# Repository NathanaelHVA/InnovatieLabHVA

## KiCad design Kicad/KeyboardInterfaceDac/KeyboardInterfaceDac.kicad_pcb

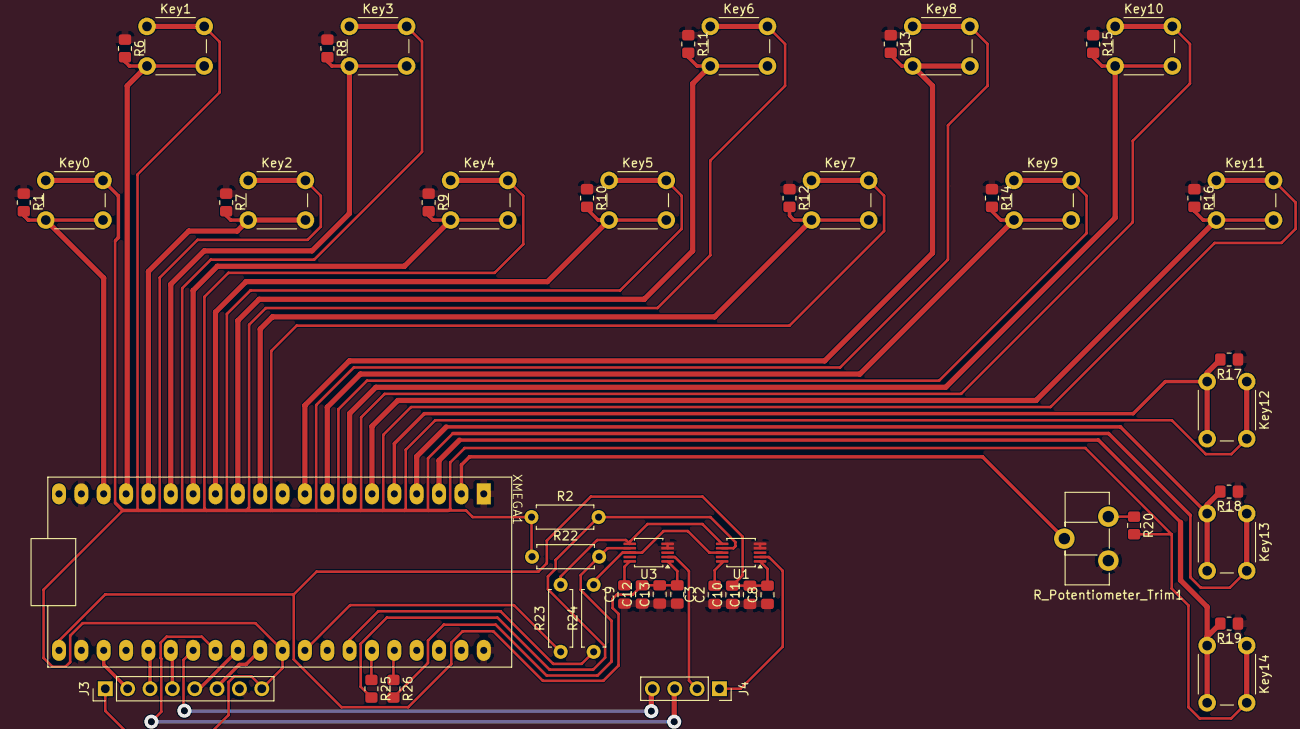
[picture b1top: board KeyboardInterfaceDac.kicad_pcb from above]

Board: 2 copper layers, 51 parts (0 on the bottom side), 38 nets.

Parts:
C2, C9: 220nF; C_0805_2012Metric_Pad1.18x1.45mm_HandSolder
C3, C8: 100nF; C_0805_2012Metric_Pad1.18x1.45mm_HandSolder
C10, C12: 0,22uF; C_0805_2012Metric_Pad1.18x1.45mm_HandSolder
C11, C13: 4,7uF; C_0805_2012Metric_Pad1.18x1.45mm_HandSolder
J3: Interface tft; PinHeader_1x08_P2.54mm_Vertical
J4: Output; PinSocket_1x04_P2.54mm_Vertical
Key0, Key1, Key2, Key3, Key4, Key5, Key6, Key7, Key8, Key9, Key10, Key11: Keyboard; SW_PUSH_6mm_H7.3mm
Key12: OctaafSelector; SW_PUSH_6mm_H7.3mm
Key13: SignaalSelector1; SW_PUSH_6mm_H7.3mm
Key14: SignaalSelector2; SW_PUSH_6mm_H7.3mm
R1, R6, R7, R8, R9, R10, R11, R12, R13, R14, R15, R16, R17, R18, R19: 10K; R_0805_2012Metric_Pad1.20x1.40mm_HandSolder
R2, R22: 10k; R_Axial_DIN0207_L6.3mm_D2.5mm_P7.62mm_Horizontal
R20: 900; R_0805_2012Metric_Pad1.20x1.40mm_HandSolder
R23, R24: 100; R_Axial_DIN0207_L6.3mm_D2.5mm_P7.62mm_Horizontal
R25, R26: 100; R_0805_2012Metric_Pad1.20x1.40mm_HandSolder
R_Potentiometer_Trim1: Potmeter/Spanningsdeler; Potentiometer_Piher_PT-10-H05_Horizontal
U1, U3: DAC80502; TSSOP-10_3x3mm_P0.5mm
XMEGA1: XMEGABoard-Rev1.11; HvA_XMEGABoard-rev1.00-S

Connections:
+5V: C3.2, C8.2, C10.2, C11.2, C12.2, C13.2, U1.1 (VDD), U3.1 (VDD), XMEGA1.21 (5V_IN)
/CS: R2.2, R22.2, R25.2, R26.2, U1.7 (~SYNC/A0), U3.7 (~SYNC/A0)
/Mosi: R24.2, U1.8 (SDIN/SDA), U3.8 (SDIN/SDA)
/SCK: R23.2, U1.6 (SCLK/SCL), U3.6 (SCLK/SCL)
GND: C2.1, C3.1, C8.1, C9.1, C10.1, C11.1, C12.1, C13.1, J3.7, R1.1, R6.1, R7.1, R8.1, R9.1, R10.1, R11.1, R12.1, R13.1, R14.1, R15.1, R16.1, R17.1, R18.1, R19.1, R_Potentiometer_Trim1.1, U1.4 (AGND), U1.5 (SPI2C), U3.4 (AGND), U3.5 (SPI2C), XMEGA1.01 (GND), XMEGA1.10 (GND), XMEGA1.19 (GND), XMEGA1.22 (GND), XMEGA1.40 (GND)
unnamed: J3.1, J3.8, Key0.1 (A), Key1.1 (A), Key2.1 (A), Key3.1 (A), Key4.1 (A), Key5.1 (A), Key6.1 (A), Key7.1 (A), Key8.1 (A), Key9.1 (A), Key10.1 (A), Key11.1 (A), Key12.1 (A), Key13.1 (A), Key14.1 (A), R2.1, R20.2, R22.1, XMEGA1.31 (3V3)
unnamed: J3.2, XMEGA1.23 (PE7)
unnamed: J3.3, XMEGA1.25 (PE5)
unnamed: J3.4, XMEGA1.26 (PE4)
unnamed: J3.5, XMEGA1.29 (PE1)
unnamed: J3.6, XMEGA1.30 (PE0)
unnamed: J4.3, XMEGA1.28 (PE2)
unnamed: J4.4, XMEGA1.27 (PE3)
unnamed: Key0.2 (B), R1.2, XMEGA1.18 (PA0)
unnamed: Key1.2 (B), R6.2, XMEGA1.17 (PA1)
unnamed: Key2.2 (B), R7.2, XMEGA1.16 (PA2)
unnamed: Key3.2 (B), R8.2, XMEGA1.15 (PA3)
unnamed: Key4.2 (B), R9.2, XMEGA1.14 (PA4)
unnamed: Key5.2 (B), R10.2, XMEGA1.13 (PA5)
unnamed: Key6.2 (B), R11.2, XMEGA1.12 (PA6)
unnamed: Key7.2 (B), R12.2, XMEGA1.11 (PA7)
unnamed: Key8.2 (B), R13.2, XMEGA1.09 (PB0)
unnamed: Key9.2 (B), R14.2, XMEGA1.08 (PB1)
unnamed: Key10.2 (B), R15.2, XMEGA1.07 (PB2)
unnamed: Key11.2 (B), R16.2, XMEGA1.06 (PB3)
unnamed: Key12.2 (B), R17.2, XMEGA1.05 (PB4)
unnamed: Key13.2 (B), R18.2, XMEGA1.04 (PB5)
unnamed: Key14.2 (B), R19.2, XMEGA1.03 (PB6)
unnamed: R20.1, R_Potentiometer_Trim1.3
unnamed: C2.2, U1.10 (VREFIO)
unnamed: C9.2, U3.10 (VREFIO)
unnamed: R_Potentiometer_Trim1.2, XMEGA1.02 (PB7)
unnamed: R26.1, XMEGA1.36 (PD3)
unnamed: R25.1, XMEGA1.35 (PD4)
unnamed: R24.1, XMEGA1.34 (PD5)
unnamed: R23.1, XMEGA1.32 (PD7)
Vout1: J4.1, U1.2 (VOUTA)
Vout2: J4.2, U3.2 (VOUTA)

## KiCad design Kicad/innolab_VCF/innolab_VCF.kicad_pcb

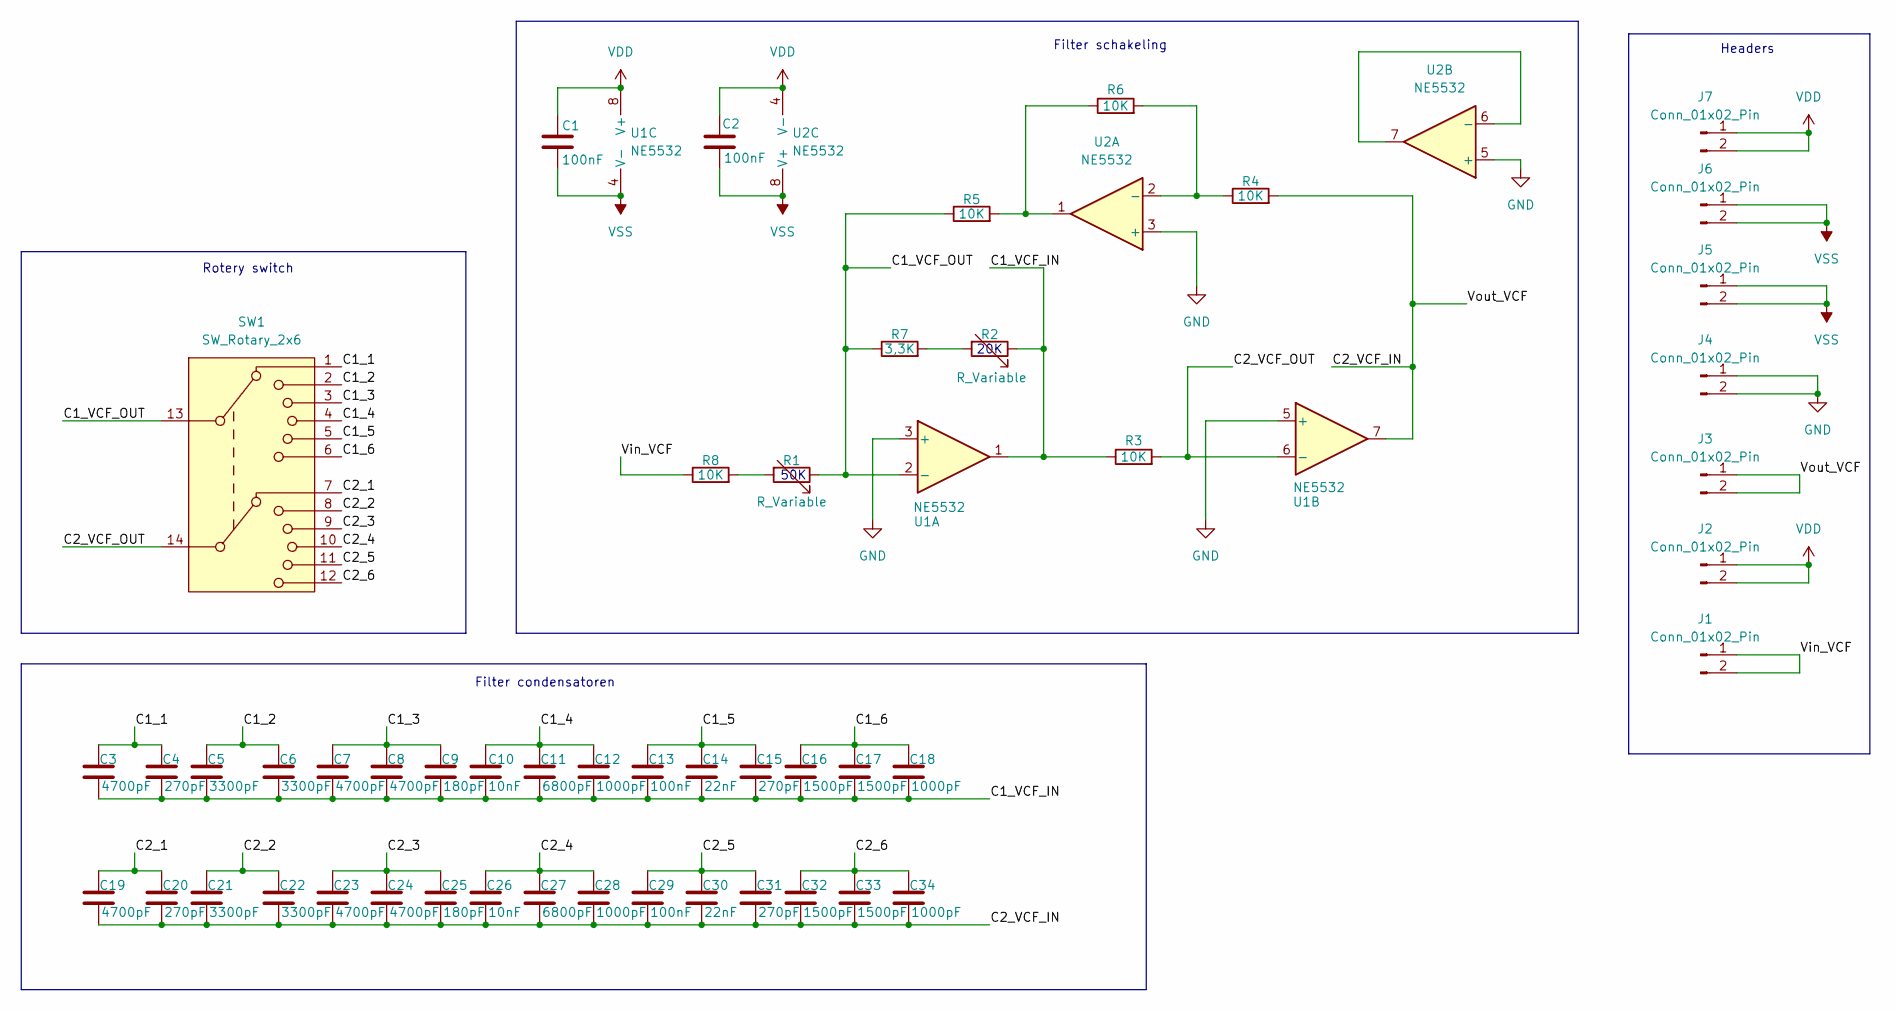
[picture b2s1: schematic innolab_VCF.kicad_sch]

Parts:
C1, C2: 100nF; C_0805_2012Metric_Pad1.18x1.45mm_HandSolder
C3, C7, C8, C19, C23, C24: 4700pF; C_Rect_L7.0mm_W2.0mm_P5.00mm
C4, C15, C20, C31: 270pF; C_0805_2012Metric
C5, C6, C21, C22: 3300pF; C_Rect_L7.0mm_W2.0mm_P5.00mm
C9, C25: 180pF; C_0805_2012Metric
C10, C26: 10nF; C_Rect_L7.0mm_W2.0mm_P5.00mm
C11, C27: 6800pF; C_Rect_L7.0mm_W2.0mm_P5.00mm
C12, C18, C28, C34: 1000pF; C_Rect_L7.0mm_W2.0mm_P5.00mm
C13, C29: 100nF; C_Rect_L7.0mm_W2.0mm_P5.00mm
C14, C30: 22nF; C_Rect_L7.0mm_W2.0mm_P5.00mm
C16, C17, C32, C33: 1500pF; C_Rect_L7.0mm_W2.0mm_P5.00mm
J1, J2, J3, J4, J5, J6, J7: Conn_01x02_Pin; PinHeader_1x02_P2.54mm_Vertical
R1, R2: R_Variable; Potentiometer_Piher_PT-10-H05_Horizontal
R3, R4, R5, R6, R8: 10K; R_0805_2012Metric_Pad1.20x1.40mm_HandSolder
R7: 3,3K; R_0805_2012Metric_Pad1.20x1.40mm_HandSolder
SW1: SW_Rotary_2x6; CK1035
U1, U2: NE5532; SOIC-8_3.9x4.9mm_P1.27mm

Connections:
/C1_1: C3.1, C4.1, SW1.1
/C1_2: C5.1, C6.1, SW1.2
/C1_3: C7.1, C8.1, C9.1, SW1.3
/C1_4: C10.1, C11.1, C12.1, SW1.4
/C1_5: C13.1, C14.1, C15.1, SW1.5
/C1_6: C16.1, C17.1, C18.1, SW1.6
/C1_VCF_IN: C3.2, C4.2, C5.2, C6.2, C7.2, C8.2, C9.2, C10.2, C11.2, C12.2, C13.2, C14.2, C15.2, C16.2, C17.2, C18.2, R2.1, R3.1, U1.1
/C1_VCF_OUT: R1.1, R5.1, R7.1, SW1.13, U1.2 (-)
/C2_1: C19.1, C20.1, SW1.7
/C2_2: C21.1, C22.1, SW1.8
/C2_3: C23.1, C24.1, C25.1, SW1.9
/C2_4: C26.1, C27.1, C28.1, SW1.10
/C2_5: C29.1, C30.1, C31.1, SW1.11
/C2_6: C32.1, C33.1, C34.1, SW1.12
/C2_VCF_IN: C19.2, C20.2, C21.2, C22.2, C23.2, C24.2, C25.2, C26.2, C27.2, C28.2, C29.2, C30.2, C31.2, C32.2, C33.2, C34.2, J3.1, J3.2, R4.2, U1.7
/C2_VCF_OUT: R3.2, SW1.14, U1.6 (-)
/Vin_VCF: J1.1, J1.2, R8.1
GND: J4.1, J4.2, U1.3 (+), U1.5 (+), U2.3 (+), U2.5 (+)
unnamed: R1.2, R8.2
unnamed: R2.2, R7.2
unnamed: R5.2, R6.1, U2.1
unnamed: R4.1, R6.2, U2.2 (-)
unnamed: U2.6 (-), U2.7
VDD: C1.1, C2.1, J2.1, J2.2, J7.1, J7.2, U1.8 (V+), U2.4 (V-)
VSS: C1.2, C2.2, J5.1, J5.2, J6.1, J6.2, U1.4 (V-), U2.8 (V+)

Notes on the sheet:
Filter schakeling
Rotery switch
50K
Filter condensatoren
20K
Headers

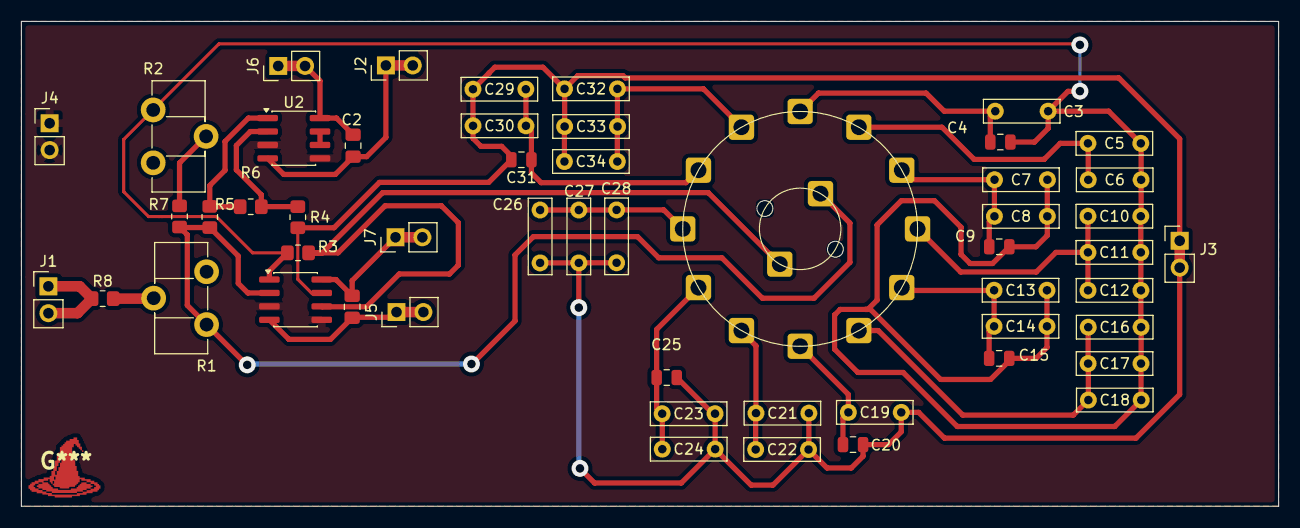
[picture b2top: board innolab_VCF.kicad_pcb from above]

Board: 2 copper layers, 118.9 x 45.8 mm, 52 parts (0 on the bottom side), 25 nets.

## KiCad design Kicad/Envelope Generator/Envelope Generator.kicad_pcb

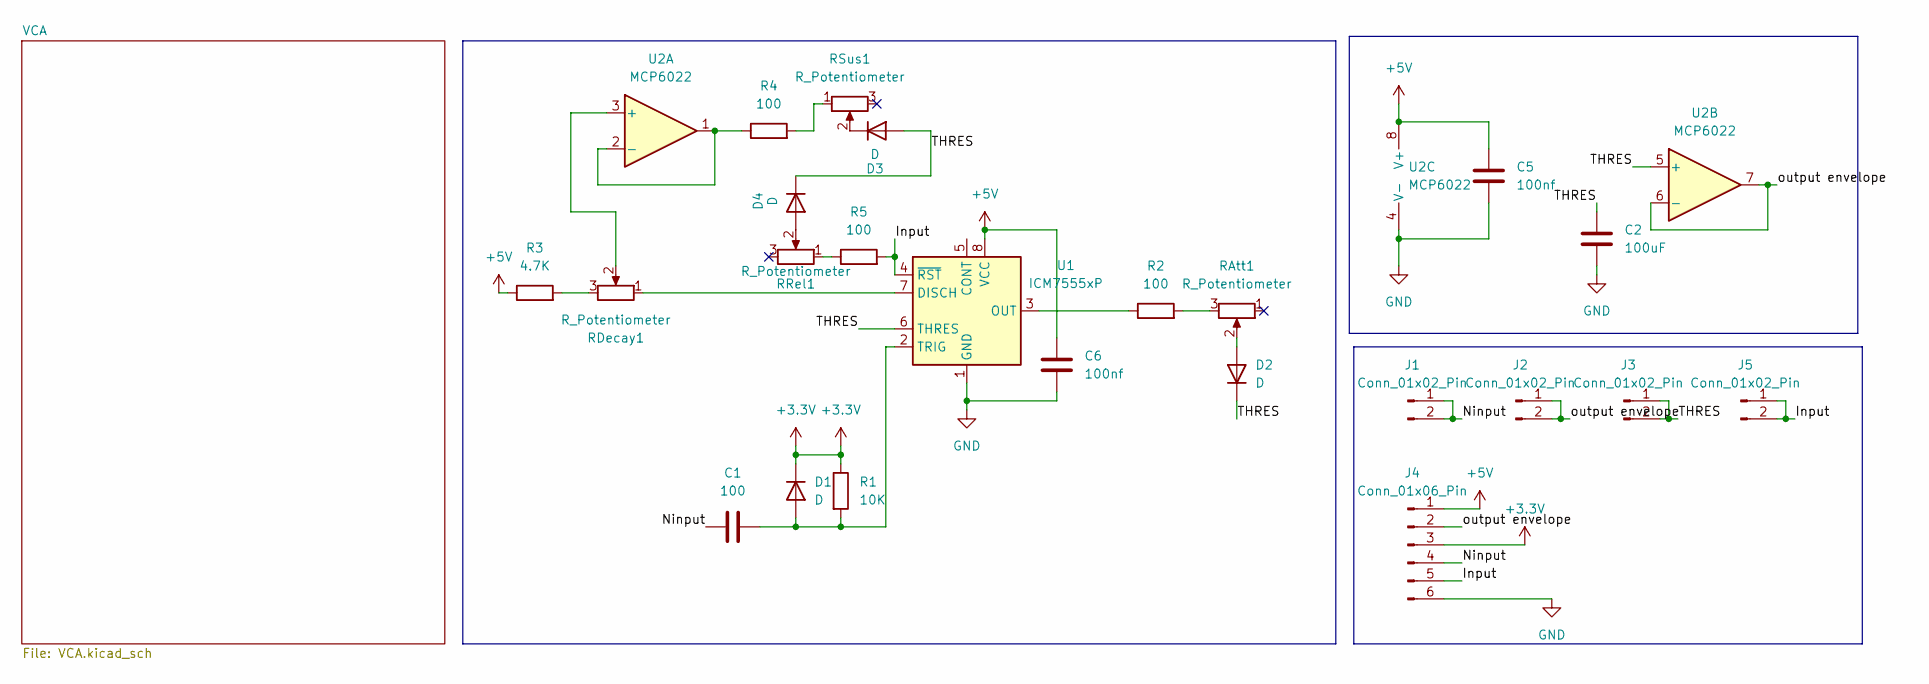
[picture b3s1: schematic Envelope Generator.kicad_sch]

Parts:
C1: 100; C_0805_2012Metric_Pad1.18x1.45mm_HandSolder
C2: 100uF; C_0805_2012Metric_Pad1.18x1.45mm_HandSolder
C5, C6: 100nf; C_0805_2012Metric_Pad1.18x1.45mm_HandSolder
D1, D2, D3, D4: D; D_0805_2012Metric_Pad1.15x1.40mm_HandSolder
J1, J2, J3, J5: Conn_01x02_Pin; PinHeader_1x02_P2.54mm_Vertical
J4: Conn_01x06_Pin; PinHeader_1x06_P2.54mm_Vertical
R1: 10K; R_0805_2012Metric_Pad1.20x1.40mm_HandSolder
R2, R4, R5: 100; R_0805_2012Metric_Pad1.20x1.40mm_HandSolder
R3: 4.7K; R_0805_2012Metric_Pad1.20x1.40mm_HandSolder
RAtt1: R_Potentiometer; Potentiometer_Piher_PT-10-H05_Horizontal
RDecay1: R_Potentiometer; Potentiometer_Piher_PT-10-H05_Horizontal
RRel1: R_Potentiometer; Potentiometer_Piher_PT-10-H05_Horizontal
RSus1: R_Potentiometer; Potentiometer_Piher_PT-10-H05_Horizontal
U1: ICM7555xP; DIP-8_W7.62mm
U2: MCP6022; SOIC-8_3.9x4.9mm_P1.27mm

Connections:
+3.3V: D1.1 (K), J4.3, R1.1
+5V: C5.2, C6.2, J4.1, R3.1, U1.8 (VCC), U2.8 (V+); also elsewhere on the board
/Input: J4.5, J5.1, J5.2, R5.2, U1.4 (~RST)
/Ninput: C1.1, J1.1, J1.2, J4.4
/THRES: C2.2, D2.1 (K), D3.2 (A), D4.1 (K), J3.1, J3.2, U1.6 (THRES), U2.5 (+)
/output envelope: J2.1, J2.2, J4.2, U2.6 (-), U2.7
GND: C2.1, C5.1, C6.1, J4.6, U1.1 (GND), U2.4 (V-); also elsewhere on the board
unnamed: C1.2, D1.2 (A), R1.2, U1.2 (TRIG)
unnamed: D2.2 (A), RAtt1.2
unnamed: D3.1 (K), RSus1.2
unnamed: D4.2 (A), RRel1.2
unnamed: R2.2, RAtt1.3
unnamed: R3.2, RDecay1.3
unnamed: R4.2, RSus1.1
unnamed: R5.1, RRel1.1
unnamed: RDecay1.1, U1.7 (DISCH)
unnamed: R2.1, U1.3 (OUT)
unnamed: RDecay1.2, U2.3 (+)
unnamed: R4.1, U2.1, U2.2 (-)

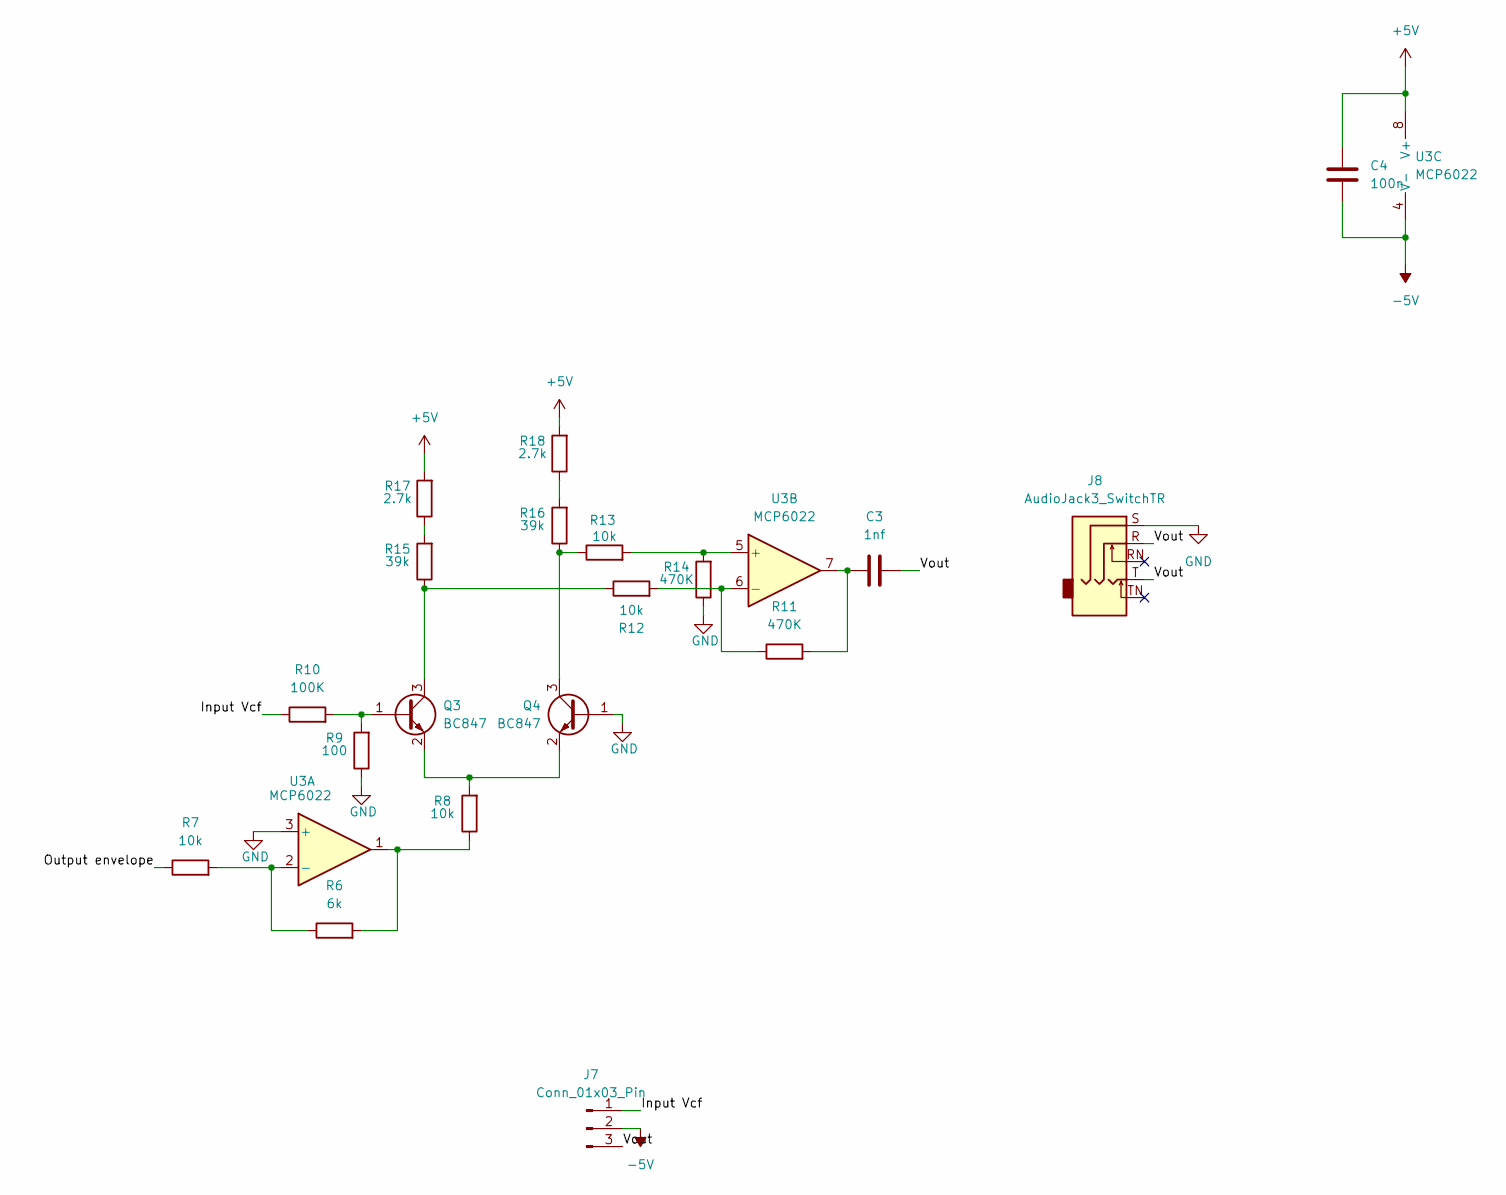
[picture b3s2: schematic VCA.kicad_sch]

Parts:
C3: 1nf; C_0805_2012Metric_Pad1.18x1.45mm_HandSolder
C4: 100n; C_0805_2012Metric_Pad1.18x1.45mm_HandSolder
J7: Conn_01x03_Pin; PinHeader_1x03_P2.54mm_Vertical
J8: AudioJack3_SwitchTR; Jack_3.5mm_CUI_SJ1-3525N_Horizontal
Q3, Q4: BC847; SOT-23
R6: 6k; C_0805_2012Metric_Pad1.18x1.45mm_HandSolder
R7, R8, R12, R13: 10k; C_0805_2012Metric_Pad1.18x1.45mm_HandSolder
R9: 100; C_0805_2012Metric_Pad1.18x1.45mm_HandSolder
R10: 100K; C_0805_2012Metric_Pad1.18x1.45mm_HandSolder
R11, R14: 470K; C_0805_2012Metric_Pad1.18x1.45mm_HandSolder
R15, R16: 39k; C_0805_2012Metric_Pad1.18x1.45mm_HandSolder
R17, R18: 2.7k; C_0805_2012Metric_Pad1.18x1.45mm_HandSolder
U3: MCP6022; SOIC-8_3.9x4.9mm_P1.27mm

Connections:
+5V: C4.2, R17.2, R18.2, U3.8 (V+); also elsewhere on the board
-5V: C4.1, J7.2, U3.4 (V-)
/VCA/Input Vcf: J7.1, R10.1
/VCA/Output envelope: R7.1
/VCA/Vout: C3.2, J7.3, J8.R, J8.T
GND: J8.S, Q4.1 (B), R9.1, R14.1, U3.3 (+); also elsewhere on the board
unnamed: C3.1, R11.2, U3.7
unnamed: Q3.1 (B), R9.2, R10.2
unnamed: Q3.3 (C), R12.1, R15.1
unnamed: Q3.2 (E), Q4.2 (E), R8.2
unnamed: Q4.3 (C), R13.1, R16.1
unnamed: R6.2, R8.1, U3.1
unnamed: R15.2, R17.1
unnamed: R16.2, R18.1
unnamed: R6.1, R7.2, U3.2 (-)
unnamed: R13.2, R14.2, U3.5 (+)
unnamed: R11.1, R12.2, U3.6 (-)

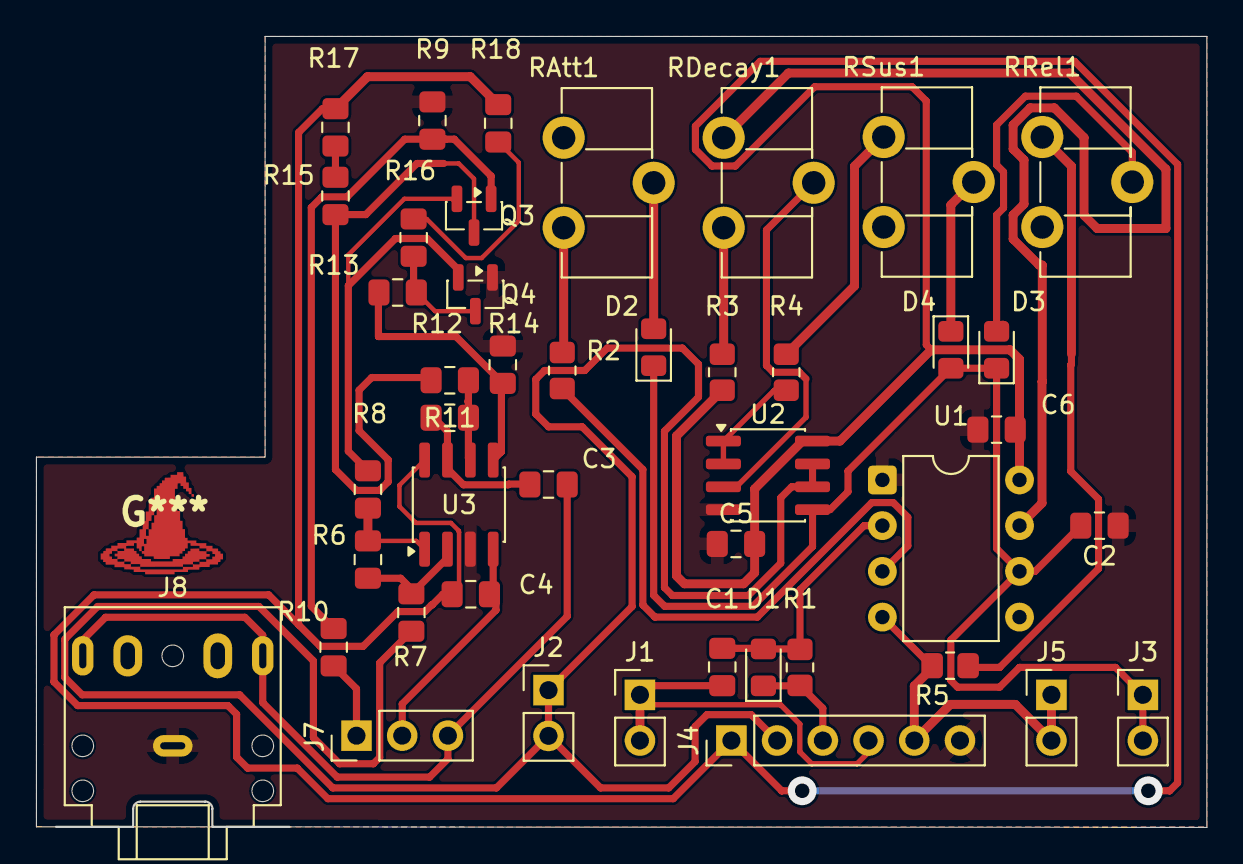
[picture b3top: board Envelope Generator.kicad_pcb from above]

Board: 2 copper layers, 65.0 x 43.9 mm, 44 parts (0 on the bottom side), 33 nets.

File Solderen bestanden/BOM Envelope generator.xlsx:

Stuklijst (BOM)
Geëxporteerd uit KiCad · 10-11-2026 · gegroepeerd per componenttype
Referentie | Aantal | Waarde | Type | Montage | Footprint | Datasheet | KiCad-footprint (volledig)
U1 | 1 | ICM7555xP | IC | THT | DIP-8 | ICM7555 datasheet (Intersil) | Package_DIP:DIP-8_W7.62mm
U2, U3 | 2 | MCP6022 | IC | SMD | SOIC-8 | MCP6022 datasheet (Microchip) | Package_SO:SOIC-8_3.9x4.9mm_P1.27mm
Q3, Q4 | 2 | BC847 | Transistor | SMD | SOT-23 | BC847 datasheet (Infineon) | Package_TO_SOT_SMD:SOT-23
D1, D2, D3, D4 | 4 | Diode (type ontbreekt) | Diode | SMD | 0805 |  | Diode_SMD:D_0805_2012Metric_Pad1.15x1.40mm_HandSolder
C1 | 1 | 100 | Condensator | SMD | 0805 |  | Capacitor_SMD:C_0805_2012Metric_Pad1.18x1.45mm_HandSolder
C2 | 1 | 100 µF | Condensator | SMD | 0805 |  | Capacitor_SMD:C_0805_2012Metric_Pad1.18x1.45mm_HandSolder
C3 | 1 | 1 nF | Condensator | SMD | 0805 |  | Capacitor_SMD:C_0805_2012Metric_Pad1.18x1.45mm_HandSolder
C4 | 1 | 100 nF | Condensator | SMD | 0805 |  | Capacitor_SMD:C_0805_2012Metric_Pad1.18x1.45mm_HandSolder
C5, C6 | 2 | 100 nF | Condensator | SMD | 0805 |  | Capacitor_SMD:C_0805_2012Metric_Pad1.18x1.45mm_HandSolder
R1 | 1 | 10 kΩ | Weerstand | SMD | 0805 |  | Resistor_SMD:R_0805_2012Metric_Pad1.20x1.40mm_HandSolder
R2, R4, R5 | 3 | 100 Ω | Weerstand | SMD | 0805 |  | Resistor_SMD:R_0805_2012Metric_Pad1.20x1.40mm_HandSolder
R3 | 1 | 4,7 kΩ | Weerstand | SMD | 0805 |  | Resistor_SMD:R_0805_2012Metric_Pad1.20x1.40mm_HandSolder
R6 | 1 | 6 kΩ | Weerstand | SMD | 0805 |  | Capacitor_SMD:C_0805_2012Metric_Pad1.18x1.45mm_HandSolder
R7, R8, R12, R13 | 4 | 10 kΩ | Weerstand | SMD | 0805 |  | Capacitor_SMD:C_0805_2012Metric_Pad1.18x1.45mm_HandSolder
R9 | 1 | 100 Ω | Weerstand | SMD | 0805 |  | Capacitor_SMD:C_0805_2012Metric_Pad1.18x1.45mm_HandSolder
R10 | 1 | 100 kΩ | Weerstand | SMD | 0805 |  | Capacitor_SMD:C_0805_2012Metric_Pad1.18x1.45mm_HandSolder
R11, R14 | 2 | 470 kΩ | Weerstand | SMD | 0805 |  | Capacitor_SMD:C_0805_2012Metric_Pad1.18x1.45mm_HandSolder
R15, R16 | 2 | 39 kΩ | Weerstand | SMD | 0805 |  | Capacitor_SMD:C_0805_2012Metric_Pad1.18x1.45mm_HandSolder
R17, R18 | 2 | 2,7 kΩ | Weerstand | SMD | 0805 |  | Capacitor_SMD:C_0805_2012Metric_Pad1.18x1.45mm_HandSolder
RAtt1, RDecay1, RRel1, RSus1 | 4 | Potmeter (waarde ontbreekt) | Potmeter | THT | Piher PT-10-H05, horizontaal |  | Potentiometer_THT:Potentiometer_Piher_PT-10-H05_Horizontal
J1, J2, J3, J5 | 4 | Pinheader 1x02 | Connector | THT | Pinheader 1x02, 2,54 mm |  | Connector_PinHeader_2.54mm:PinHeader_1x02_P2.54mm_Vertical
J4 | 1 | Pinheader 1x06 | Connector | THT | Pinheader 1x06, 2,54 mm |  | Connector_PinHeader_2.54mm:PinHeader_1x06_P2.54mm_Vertical
J7 | 1 | Pinheader 1x03 | Connector | THT | Pinheader 1x03, 2,54 mm |  | Connector_PinHeader_2.54mm:PinHeader_1x03_P2.54mm_Vertical
J8 | 1 | Audiojack 3,5 mm (TR, schakelend) | Connector | THT | Jack 3,5 mm CUI SJ1-3525N, horizontaal |  | Connector_Audio:Jack_3.5mm_CUI_SJ1-3525N_Horizontal
Totaal | 44
Het totaal past zich aan als je de filter gebruikt (SUBTOTAL). Gele cellen in '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

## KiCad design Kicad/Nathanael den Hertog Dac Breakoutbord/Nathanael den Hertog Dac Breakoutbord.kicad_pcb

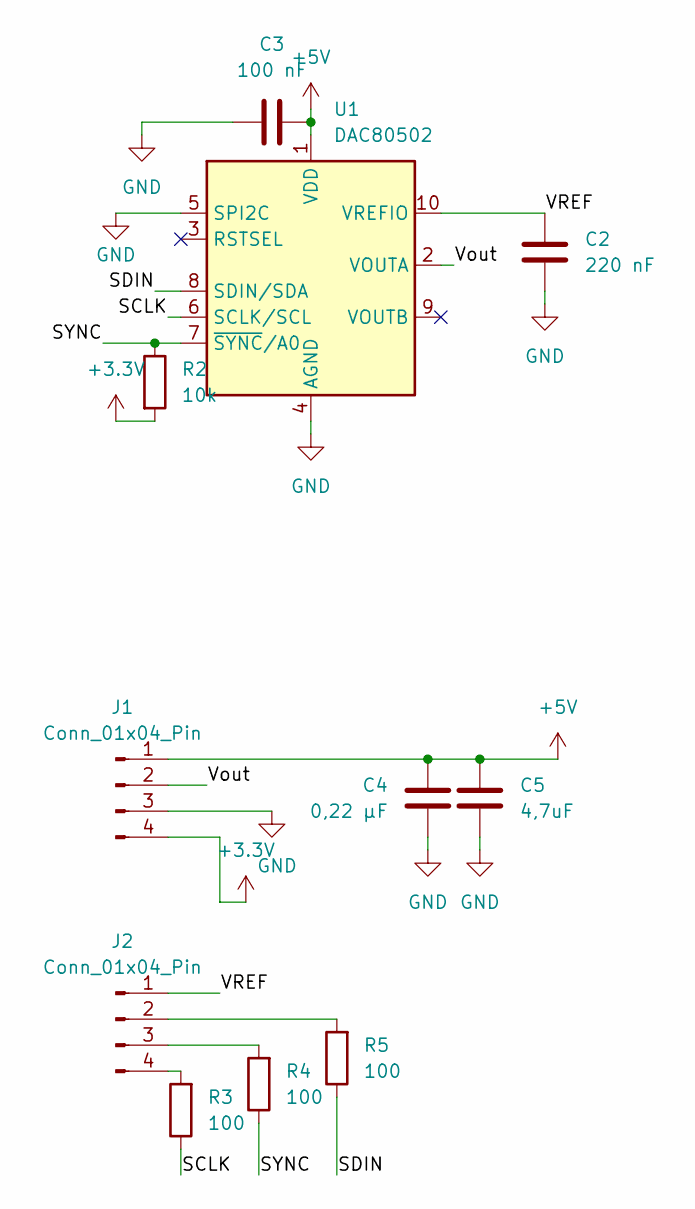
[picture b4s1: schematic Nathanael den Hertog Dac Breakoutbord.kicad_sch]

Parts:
C2: 220 nF; C_0805_2012Metric_Pad1.18x1.45mm_HandSolder
C3: 100 nF; C_0805_2012Metric_Pad1.18x1.45mm_HandSolder
C4: 0,22 µF; C_0805_2012Metric_Pad1.18x1.45mm_HandSolder
C5: 4,7uF; C_0805_2012Metric_Pad1.18x1.45mm_HandSolder
J1, J2: Conn_01x04_Pin; PinHeader_1x04_P2.54mm_Vertical
R2: 10k; R_0805_2012Metric_Pad1.20x1.40mm_HandSolder
R3, R4, R5: 100; R_0805_2012Metric_Pad1.20x1.40mm_HandSolder
U1: DAC80502; TSSOP-10_3x3mm_P0.5mm

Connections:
+3.3V: J1.4, R2.2
+5V: C3.2, C4.2, C5.2, J1.1, U1.1 (VDD)
/SCLK: R3.1, U1.6 (SCLK/SCL)
/SDIN: R5.1, U1.8 (SDIN/SDA)
/SYNC: R2.1, R4.1, U1.7 (~SYNC/A0)
/VREF: C2.1, J2.1, U1.10 (VREFIO)
/Vout: J1.2, U1.2 (VOUTA)
GND: C2.2, C3.1, C4.1, C5.1, J1.3, U1.4 (AGND), U1.5 (SPI2C)
unnamed: J2.2, R5.2
unnamed: J2.3, R4.2
unnamed: J2.4, R3.2

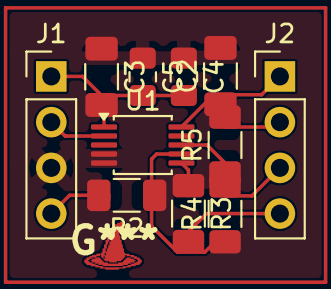
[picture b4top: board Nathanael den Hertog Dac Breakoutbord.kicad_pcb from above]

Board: 2 copper layers, 11 parts (0 on the bottom side), 11 nets.

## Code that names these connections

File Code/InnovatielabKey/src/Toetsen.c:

#include <avr/io.h>
#include "toetsen.h"

// Octaafknop op PB4
#define OCTAAF_PORT     PORTB
#define OCTAAF_PIN_bm   PIN4_bm
#define OCTAAF_PINCTRL  PIN4CTRL
#define OCTAAF_BIT      12     

#define TOETS10_BIT     10
#define TOETS10_PORT    PORTC
#define TOETS10_PIN_bm  PIN0_bm
#define TOETS10_PINCTRL PIN0CTRL

static uint8_t  octaaf         = 0;
static uint16_t vorige_sample  = 0; 
static uint16_t vorige_stabiel = 0;   

void toetsen_init(void)
{
    PORTA.DIRCLR = 0xFF;                 // PA0..PA7 als ingang
    PORTB.DIRCLR = 0x0B;                 // PB0, PB1, PB3 als ingang (PB2 = DAC)
    TOETS10_PORT.DIRCLR = TOETS10_PIN_bm;// PC0 als ingang
    OCTAAF_PORT.DIRCLR = OCTAAF_PIN_bm;  // PB4 als ingang

    // Interne pull-downs
    for (uint8_t i = 0; i < 8; i++)
        (&PORTA.PIN0CTRL)[i] = PORT_OPC_PULLDOWN_gc;
    for (uint8_t i = 0; i < 4; i++)
        if (i != 2)                      // PB2 overslaan, die is de DAC-uitgang
            (&PORTB.PIN0CTRL)[i] = PORT_OPC_PULLDOWN_gc;
    TOETS10_PORT.TOETS10_PINCTRL = PORT_OPC_PULLDOWN_gc;
    OCTAAF_PORT.OCTAAF_PINCTRL = PORT_OPC_PULLDOWN_gc;
}

// Alle knoppen in één 16-bit waarde:
// bit 0..7 = PA0..PA7, bit 8, 9, 11 = PB0, PB1, PB3,
// bit 10 = PC0 (toets 10), bit 12 = octaafknop
static uint16_t lees_knoppen(void)
{
    uint16_t a   = PORTA.IN;
    uint16_t b   = PORTB.IN & 0x0B;      // PB0, PB1, PB3 -> bit 8, 9, 11
    uint16_t t10 = (TOETS10_PORT.IN & TOETS10_PIN_bm) ? 1U : 0U;
    uint16_t o   = (OCTAAF_PORT.IN & OCTAAF_PIN_bm) ? 1U : 0U;

    return a | (b << 8) | (t10 << TOETS10_BIT) | (o << OCTAAF_BIT);
}

toetsen_event_t toetsen_poll(void)
{
    toetsen_event_t ev = {0, 0};
    uint16_t nu = lees_knoppen();

    // Debounce: alleen accepteren als twee polls na elkaar gelijk zijn
    if (nu == vorige_sample) {
        uint16_t nieuw = nu & ~vorige_stabiel;   // laag-naar-hoog overgangen

        ev.toetsen = nieuw & ((1U << AANTAL_TOETSEN) - 1);

        if (nieuw & (1U << OCTAAF_BIT)) {
            ev.octaaf = 1;
            octaaf = (octaaf >= OCTAAF_MAX) ? 0 : octaaf + 1;
        }

        vorige_stabiel = nu;
    }
    vorige_sample = nu;

    return ev;
}

uint8_t toetsen_octaaf(void)
{
    return octaaf;
}

char toetsen_poort(uint8_t toets)
{
    if (toets < 8)             return 'A';
    if (toets == TOETS10_BIT)  return 'C';
    return 'B';
}

uint8_t toetsen_pin(uint8_t toets)
{
    if (toets < 8)             return toets;
    if (toets == TOETS10_BIT)  return 0;
    return toets - 8;
}

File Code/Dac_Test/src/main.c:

/*!
 * \file    main.c
 * \brief   Pure signaalgenerator: 1 of 2 externe DAC80501 (SPI), 4 golfvormen, frequentie intypen
 *
 * Zo werkt het, van typen tot signaal:
 *   1. Jij typt in de terminal bijvoorbeeld 440 + Enter.
 *   2. freq_input_poll() maakt van die tekens een getal in centi-Hz (440 Hz = 44000).
 *   3. setFreq_centihz() rekent dat om naar een "stap" per sample (vco_step).
 *   4. Een timer (TCC0) tikt FS keer per seconde. In die ISR doen we elke tik:
 *          fase += stap  ->  waarde opzoeken in de golftabel  ->  naar de DAC sturen
 *      Een grote stap = de golf wordt sneller doorlopen = hogere frequentie.
 *
 * Wat je kunt instellen:
 *   - aantal DAC's (1 of 2)  : DAC_AANTAL in dac80501.h (of -DDAC_AANTAL=2)
 *   - golfvorm per VCO       : VCO1_GOLF en VCO2_GOLF hieronder
 *   - toonhoogte van VCO 2   : VCO2_RATIO_Q8 hieronder
 *   - frequentie             : intypen in de terminal, of START_FREQ_CENTIHZ voor bij het opstarten
 *
 * Pinnen: zie dac80501.h (SCLK = PD7, SDIN = PD5, SYNC DAC 1 = PD4, SYNC DAC 2 = PF4)
 */

#define F_CPU 32000000UL               // vóór de includes, één keer (klok gaat naar 32 MHz)

#include <avr/io.h>
#include <avr/interrupt.h>
#include <util/atomic.h>
#include <stdio.h>
#include <stdint.h>
#include <math.h>

#include "serialF0.h"
#include "dac80501.h"
#include "freq_input.h"

/* ---------- instellingen ---------- */

// Samplefrequentie van de VCO's. Per sample gaan er twee SPI-frames van 24 bit over de bus
// (3 us) en de ISR zelf kost ongeveer 9 us (geschat uit de assembly, niet gemeten).
// Bij 100 kHz is de CPU dan bijna vol (10 us per sample); 90 kHz is nog net werkbaar.
// (Dat geldt voor 2 DAC's. Bij DAC_AANTAL 1 gaat er één frame over de bus en wordt maar één VCO berekend.)
#define FS 90000UL

// 1 = lineair interpoleren tussen twee tabelpunten (veel schoner signaal, kost per DAC ongeveer 1-2 us
//     extra in de ISR, niet gemeten); 0 = gewoon het dichtstbijzijnde tabelpunt (blokkerig, ~37 dB SNR)
#define VCO_INTERPOLATIE 1

// Golfvorm per VCO: GOLF_SINUS, GOLF_BLOK, GOLF_ZAAGTAND of GOLF_DRIEHOEK
#define VCO1_GOLF       GOLF_SINUS
#define VCO2_GOLF       GOLF_ZAAGTAND

// Toonhoogte van VCO 2 t.o.v. VCO 1 in 1/256: 256 = gelijk, 512 = een octaaf hoger, 257 = lichte detune
#define VCO2_RATIO_Q8   256UL

// Frequentie bij het opstarten, in centi-Hz (100000 = 1000,00 Hz)
#define START_FREQ_CENTIHZ  100000UL

/* ---------- afgeleide waarden (niet aanpassen) ---------- */

// De timer telt in hele klokpulsen, dus de echte samplefrequentie wijkt een beetje af van FS
// (32 MHz / 355 = 90140 Hz i.p.v. 90000 Hz). Voor de stap rekenen we met de echte waarde,
// anders klopt de frequentie niet precies.
#define FS_DIV    (F_CPU / FS)         // klokpulsen per sample
#define FS_ECHT   (F_CPU / FS_DIV)     // echte samplefrequentie in Hz

/* ---------- golfvormen en VCO's ---------- */

typedef enum { GOLF_SINUS, GOLF_BLOK, GOLF_ZAAGTAND, GOLF_DRIEHOEK, GOLF_AANTAL } golf_t;

static const char *golf_naam[GOLF_AANTAL] = { "sinus", "blok", "zaagtand", "driehoek" };

static uint16_t golf_tabel[GOLF_AANTAL][256];   // 16-bit tabellen voor de DAC80501

static uint32_t                   vco_phase[2];  // alleen de ISR schrijft hierin
static volatile uint32_t          vco_step[2];
static const uint16_t * volatile  vco_lut[2];

// Tabelwaarde bij een 32-bit fase: bovenste 8 bit = tabelindex, de 8 bit daaronder = fractie
static inline uint16_t lut_waarde(const uint16_t *lut, uint32_t phase) {
#if VCO_INTERPOLATIE
    uint8_t  i  = (uint8_t)(phase >> 24);
    uint8_t  fr = (uint8_t)(phase >> 16);
    uint16_t a  = lut[i];
    uint16_t b  = lut[(uint8_t)(i + 1)];            // na punt 255 weer naar punt 0
    int32_t  d  = (int32_t)b - (int32_t)a;
    return (uint16_t)(a + ((d * fr) >> 8));
#else
    return lut[phase >> 24];
#endif
}

// De sampleklok: elke tik één nieuwe waarde naar elke DAC
ISR(TCC0_OVF_vect) {
    vco_phase[0] += vco_step[0];
    dac80501_write(DAC_EXT1, lut_waarde(vco_lut[0], vco_phase[0]));
#if DAC_AANTAL > 1
    vco_phase[1] += vco_step[1];
    dac80501_write(DAC_EXT2, lut_waarde(vco_lut[1], vco_phase[1]));
#endif
}

// frequentie in centi-Hz (440 Hz = 44000); VCO 2 volgt VCO 1 met VCO2_RATIO_Q8
// stap = f / FS * 2^32  (de fase loopt van 0 tot 2^32 = één periode)
static void setFreq_centihz(uint32_t f_centi) {
    uint32_t s1 = (uint32_t)(((uint64_t)f_centi << 32) / (FS_ECHT * 100UL));
    uint32_t s2 = (uint32_t)(((uint64_t)s1 * VCO2_RATIO_Q8) >> 8);
    ATOMIC_BLOCK(ATOMIC_RESTORESTATE) { vco_step[0] = s1; vco_step[1] = s2; }
}

// golfvorm van een VCO wisselen (vco = 0 of 1)
static void vco_set_golf(uint8_t vco, golf_t golf) {
    ATOMIC_BLOCK(ATOMIC_RESTORESTATE) { vco_lut[vco] = golf_tabel[golf]; }
}

// Een via de seriële poort ingetypte frequentie (bijvoorbeeld "440" + Enter) meteen toepassen
static void serieel_frequentie(void) {
    uint32_t f;
    if (freq_input_poll(&f)) {
        setFreq_centihz(f);
        printf("\nFrequentie: %lu.%02lu Hz\n",
               (unsigned long)(f / 100),
               (unsigned long)(f % 100));
    }
}

static void klok_32mhz(void) {
    OSC.CTRL |= OSC_RC32MEN_bm;
    while (!(OSC.STATUS & OSC_RC32MRDY_bm));
    CCP = CCP_IOREG_gc;
    CLK.CTRL = CLK_SCLKSEL_RC32M_gc;
}

static void golf_init(void) {
    for (int i = 0; i < 256; i++) {
        golf_tabel[GOLF_SINUS][i]    = (uint16_t)(32767.5 + 32767.0 * sin(2 * M_PI * i / 256.0));
        golf_tabel[GOLF_BLOK][i]     = (i < 128) ? 65535 : 0;
        golf_tabel[GOLF_ZAAGTAND][i] = (uint16_t)((uint32_t)i * 65535UL / 255UL);
        golf_tabel[GOLF_DRIEHOEK][i] = (uint16_t)((uint32_t)((i < 128) ? i : 255 - i) * 65535UL / 127UL);
    }
    vco_set_golf(0, VCO1_GOLF);
    vco_set_golf(1, VCO2_GOLF);

    // Timer TCC0 als sampleklok: ISR elke FS_DIV klokpulsen
    TCC0.PER = FS_DIV - 1;
    TCC0.INTCTRLA = TC_OVFINTLVL_HI_gc;
    TCC0.CTRLA = TC_CLKSEL_DIV1_gc;
    PMIC.CTRL |= PMIC_HILVLEN_bm;
}

/* ---------- main ---------- */

int main(void)
{
    klok_32mhz();
    init_stream(F_CPU);
    dac80501_init();           // SPID + de DAC('s) instellen (DAC_AANTAL)
    golf_init();               // tabellen + sampleklok (de ISR schrijft naar de DAC's)
    setFreq_centihz(START_FREQ_CENTIHZ);
    sei();                     // pas hierna kan printf versturen (TX werkt met interrupts)

    printf("\nSignaalgenerator, %u DAC(s)\n", (unsigned)DAC_AANTAL);
    printf("DAC 1: %s", golf_naam[VCO1_GOLF]);
#if DAC_AANTAL > 1
    printf("   DAC 2: %s", golf_naam[VCO2_GOLF]);
#endif
    printf("\nTyp een frequentie (440 of 261.63) + Enter\n");

    while (1) {
        serieel_frequentie();  // niet-blokkerend: kijkt of er nieuwe tekens zijn
    }
}
